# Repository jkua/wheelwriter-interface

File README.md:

# Low-level IBM Wheelwriter interface
This project is to build a low-level interface for an IBM Wheelwriter 
typewriter. This builds on work by 
[tofergregg](https://github.com/tofergregg/IBM-Wheelwriter-Hack), 
[RussellSenior](https://github.com/tofergregg/IBM-Wheelwriter-Hack/pull/11), 
and [jim11662418](https://github.com/jim11662418/wheelwriter-teletype) 
who figured out the internal serial communication bus and the protocol it uses.

This project was built and tested on an IBM Wheelwriter 3. Likely this will 
work on at least Series I Wheelwriters (3/5/6), and possibly later models as 
well.

## Architecture
This project consists of:

1. [Hardware interface module](pcb/) - this attaches to the back of the Wheelwriter as
the OEM printer option did, and connect to the 10-pin option connector located 
behind the 70 mm-wide hinged panel on the top rear of the typewriter. The core 
electronics are an [Arduino Nano RP2040 Connect](https://docs.arduino.cc/hardware/nano-rp2040-connect)
mounted on a custom PCB to interface with the Wheelwriter's option connector. 

3. [Arduino Wheelwriter driver](src/arduino/wheelwriter_interface) - this 
communicates with the Wheelwriter over the serial bus and provide low-level 
control of the typewriter, including platen and carriage positioning and 
typehead imprinting.

4. [REST API](docs/wwib_rest_api.md) service - the built-in WiFi connectivity 
on the Nano supports a web server which allows a modern computer, smartphone, 
or tablet to control the typewriter via the interface module.

5. [Python serial client](src/client) - PC client to talk to the Arduino and
allow it to send text to print as well as relay raw Wheelwriter commands. 

6. REST Client software - this software will demonstrate the use of the REST API

## Related work
[IBM-Wheelwriter-Hack](https://github.com/tofergregg/IBM-Wheelwriter-Hack) by 
Chris Gregg/[tofergregg](https://github.com/tofergregg) is what initially 
inspired me to look into Wheelwriters. His [videos](https://www.youtube.com/watch?v=Awxbu8y5cv8) 
[on](https://www.youtube.com/watch?v=0vrvDQmZcPI) 
[YouTube](https://www.youtube.com/watch?v=5FTS4fj5Im4) showed his work on 
reverse engineering the Wheelwriter's bus with a logic analyzer in about 2017.
His implementation bit-bangs a TX line to drive a N-channel MOSFET.

Be sure to check out his 
[Smith Corona typewriter to printer conversion](https://www.youtube.com/watch?v=le4C2HeNrdQ)!

Ryan Jarvis/[Cabalist](https://github.com/Cabalist) provided a 
[complete printwheel mapping](https://github.com/tofergregg/IBM-Wheelwriter-Hack/issues/5) 
for US language printwheels.

[Russell Senior](https://github.com/RussellSenior) made the connection that 
this is an Intel 8051 9-bit serial bus in mode 2 and provided a 
[great wiki page](https://github.com/RussellSenior/IBM-Wheelwriter-Hack/wiki/Bus-Protocol) 
describing a great deal of the command set.

[jim11662418](https://github.com/jim11662418) created implementations for 
the 8051 compatible [Dallas Semi DS89C440](https://github.com/jim11662418/wheelwriter-printer)
and [STC Micro STC15W4K32S4](https://github.com/jim11662418/wheelwriter-teletype)
that are very nice.

[MicroCoreLabs](https://github.com/MicroCoreLabs) created an 
[Lattice FPGA implementation](https://github.com/MicroCoreLabs/Projects/tree/master/Wheelwriter) 
and an [Arduino Leonardo implementation](https://github.com/MicroCoreLabs/Projects/tree/master/Wheelwriter2). 
Both implement a serial port that translates an ASCII character stream to motor 
controller commands. The Arduino implementation directly uses the ATmega32u4's 
UART an interestingly toggles the transmitter off when not sending. 
[Here's a YouTube video](https://www.youtube.com/watch?v=q8gCYw75E1A) of the 
FPGA version running.

[CadetWriter](https://github.com/IBM-1620/Cadetwriter) is an effort by Dave 
Babcock and Stephen Casner to interface to a Wheelwriter 1000 by instead 
sitting between the keyboard and the logic controller. This work was developed 
to build a general-purpose ASCII terminal.

### Derived work that builds on this project
[Generative Daily Planner](https://www.thingswemake.com/generative-daily-planner)
([Github](https://github.com/joshsucher/wheelwriter-gpt-agenda)) by Josh 
Sucher, is a "GPT-4-powered bot that ingests email, calendar and contacts from 
a range of sources (mainly Gmail, Gcal and iCloud) and outputs a daily agenda".

[wheelwriter6-printer](https://github.com/knicknackery/wheelwriter6-printer) 
by Brad/[knickknackery](https://github.com/knicknackery) ports this to a Pico W to interface a Wheelwriter 6 Series II with a CUPS 
driver to convert a Wheelwriter into a wireless printer! Includes a custom font 
for the WW6 Courier 12 wheel for a WYWISYG experience

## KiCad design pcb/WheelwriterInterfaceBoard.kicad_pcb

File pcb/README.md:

# Wheelwriter Interface Board

There are two versions of the Wheelwriter Interface Board. 

## v1 - Prototype breadboard
v1 ([schematic](wwib-v1/wwib-v1_schematic.pdf)) is the original prototype and 
was wired up on a solderless breadboard. This is what the code base was 
developed on as of 2024-09-21. This design is based on 
[tofergregg's](https://github.com/tofergregg/IBM-Wheelwriter-Hack) work.

## v2 - Expansion housing PCB
v2 ([schematic](wwib-v2/WheelwriterInterfaceBoard_schematic.pdf)) was designed 
to be a fabricated PCB and be the same size as the original Wheelwriter 
expansion boards, fit in the original expansion housing, and connect to the 
Wheelwriter expansion interface connector via a cable. This design has and 
isolated power supply and bus interface and is powered by the typewriter 
instead of the Arduino's USB port. 

*While I have not tested this design, [BlipRanger](https://github.com/BlipRanger)
has [reported success](https://github.com/jkua/wheelwriter-interface/issues/2#issuecomment-2415313493)!*

### Expansion cable
The expansion port on the Wheelwriter is a Molex SL series 10-pin shrouded 
header. A short cable needs to be built to connect the Wheelwriter expansion 
port to this interface board. A mating connector is Molex 50-57-9210 
(70066-0079). Contacts for 22-24 AWG wire are Molex 16-02-0102 (70058-0222). 

This design only uses +5V (pins 1, 2), GND (pins 3, 4), and BUS (pin 5). The 
rest are only for testing.

### v2 mounted in expansion housing

## Reference
### Original Wheelwriter expansion board
Image of the back of the board

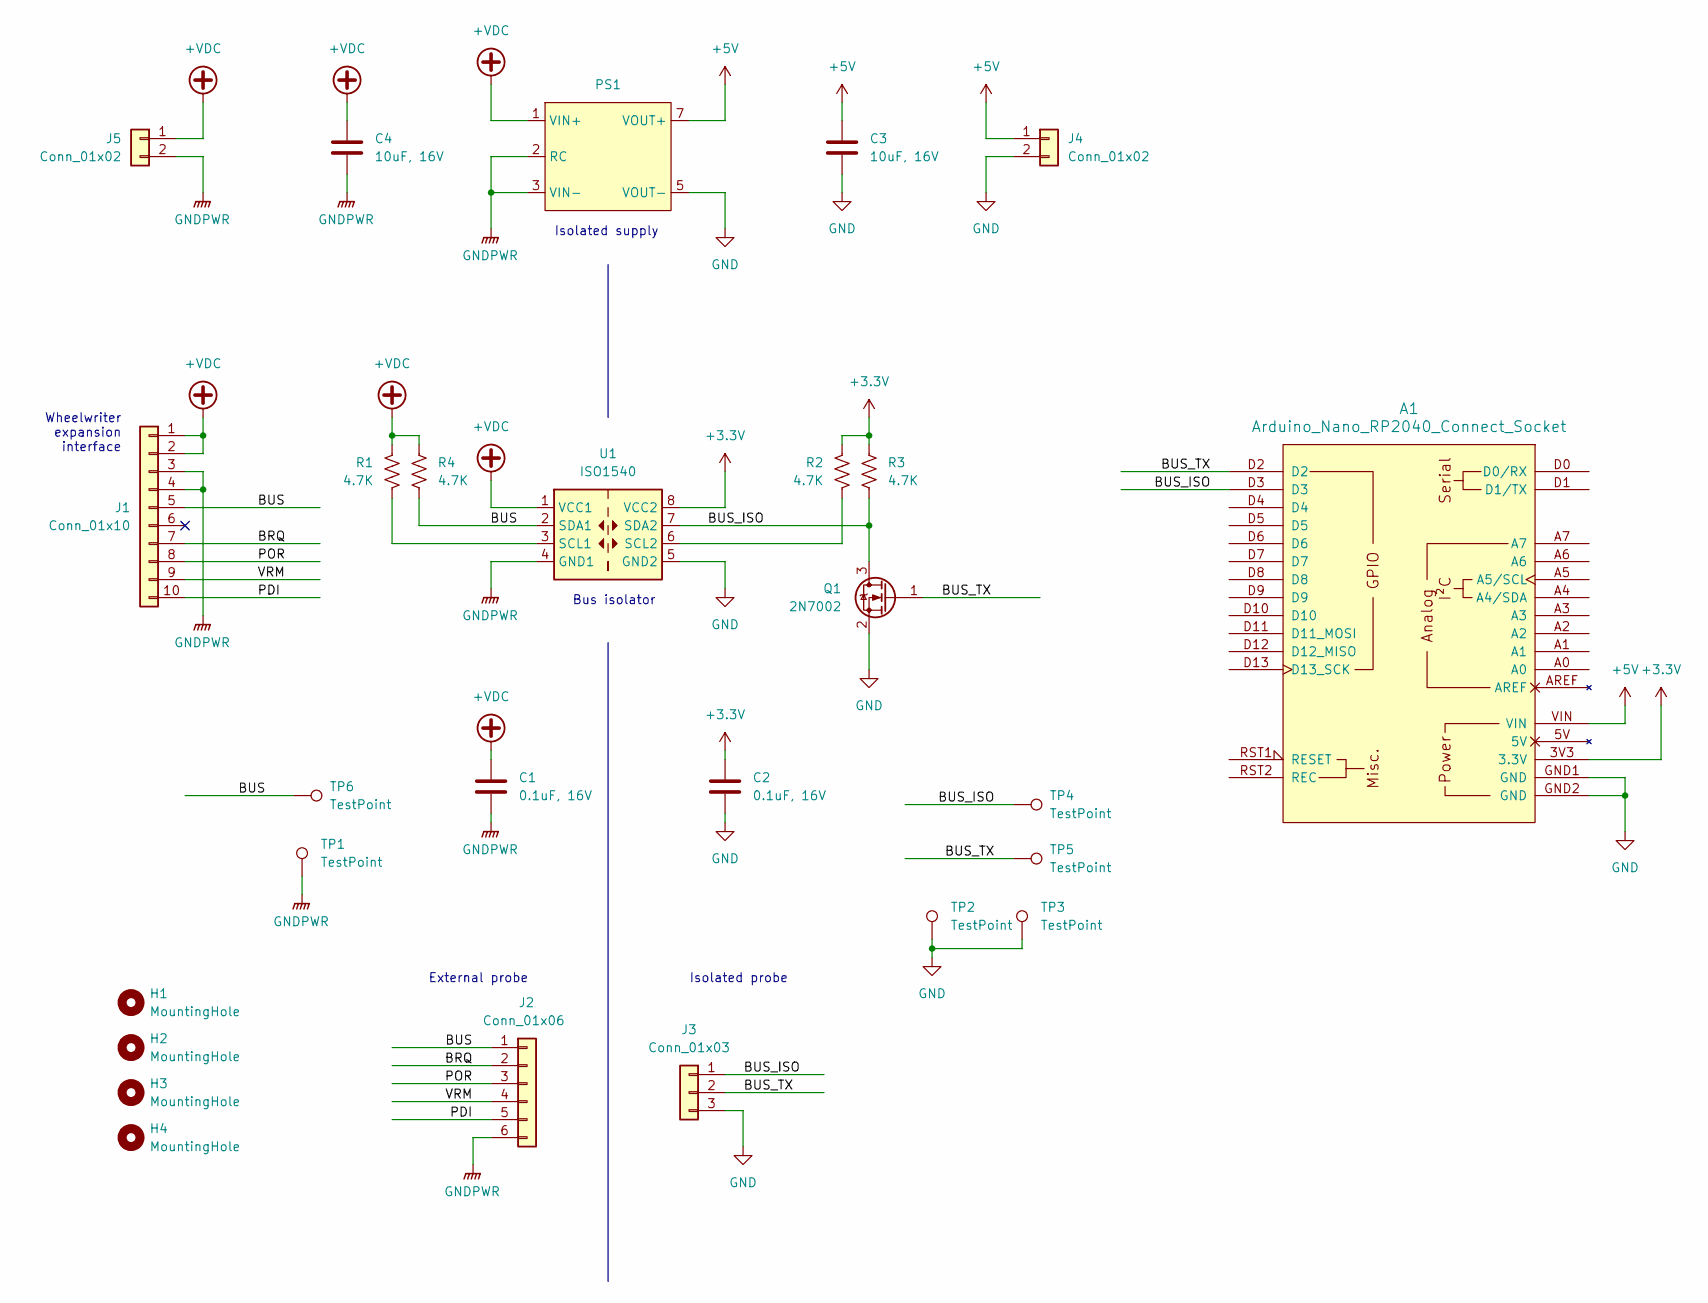
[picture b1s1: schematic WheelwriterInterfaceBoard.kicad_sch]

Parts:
A1: Arduino_Nano_RP2040_Connect_Socket; Arduino_Nano_Every_Socket
C1, C2: 0.1uF, 16V; C_0805_2012Metric_Pad1.18x1.45mm_HandSolder
C3, C4: 10uF, 16V; C_0805_2012Metric_Pad1.18x1.45mm_HandSolder
H1, H2, H3, H4: MountingHole; MountingHole_160mil
J1: Conn_01x10; Molex SL 70541-0009
J2: Conn_01x06; PinHeader_1x06_P2.54mm_Vertical
J3: Conn_01x03; PinHeader_1x03_P2.54mm_Vertical
J4, J5: Conn_01x02; PinHeader_1x02_P2.54mm_Vertical
PS1: Converter_DCDC_TDK-Lambda_CC10(R)
Q1: 2N7002; SOT-23
R1, R2, R3, R4: 4.7K; R_0805_2012Metric_Pad1.20x1.40mm_HandSolder
TP1, TP2, TP3, TP4, TP5, TP6: TestPoint; TestPoint_Keystone_5005-5009_Compact
U1: ISO1540; SOIC-8_3.9x4.9mm_P1.27mm

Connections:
+3.3V: A1.3V3 (3.3V), C2.1, R2.1, R3.1, U1.8 (VCC2)
+5V: A1.VIN, C3.1, J4.1, PS1.7 (VOUT+)
+VDC: C1.1, C4.1, J1.1, J1.2, J5.1, PS1.1 (VIN+), R1.1, R4.1, U1.1 (VCC1)
/BRQ: J1.7, J2.2
/BUS: J1.5, J2.1, R4.2, TP6.1, U1.2 (SDA1)
/BUS_ISO: A1.D3, J3.1, Q1.3 (D), R3.2, TP4.1, U1.7 (SDA2)
/BUS_TX: A1.D2, J3.2, Q1.1 (G), TP5.1
/PDI: J1.10, J2.5
/POR: J1.8, J2.3
/VRM: J1.9, J2.4
GND: A1.GND1 (GND), A1.GND2 (GND), C2.2, C3.2, J3.3, J4.2, PS1.5 (VOUT-), Q1.2 (S), TP2.1, TP3.1, U1.5 (GND2)
GNDPWR: C1.2, C4.2, J1.3, J1.4, J2.6, J5.2, PS1.2 (RC), PS1.3 (VIN-), TP1.1, U1.4 (GND1)
unnamed: R1.2, U1.3 (SCL1)
unnamed: R2.2, U1.6 (SCL2)

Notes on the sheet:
External probe
Bus isolator
Isolated supply
Wheelwriter expansion interface
Isolated probe

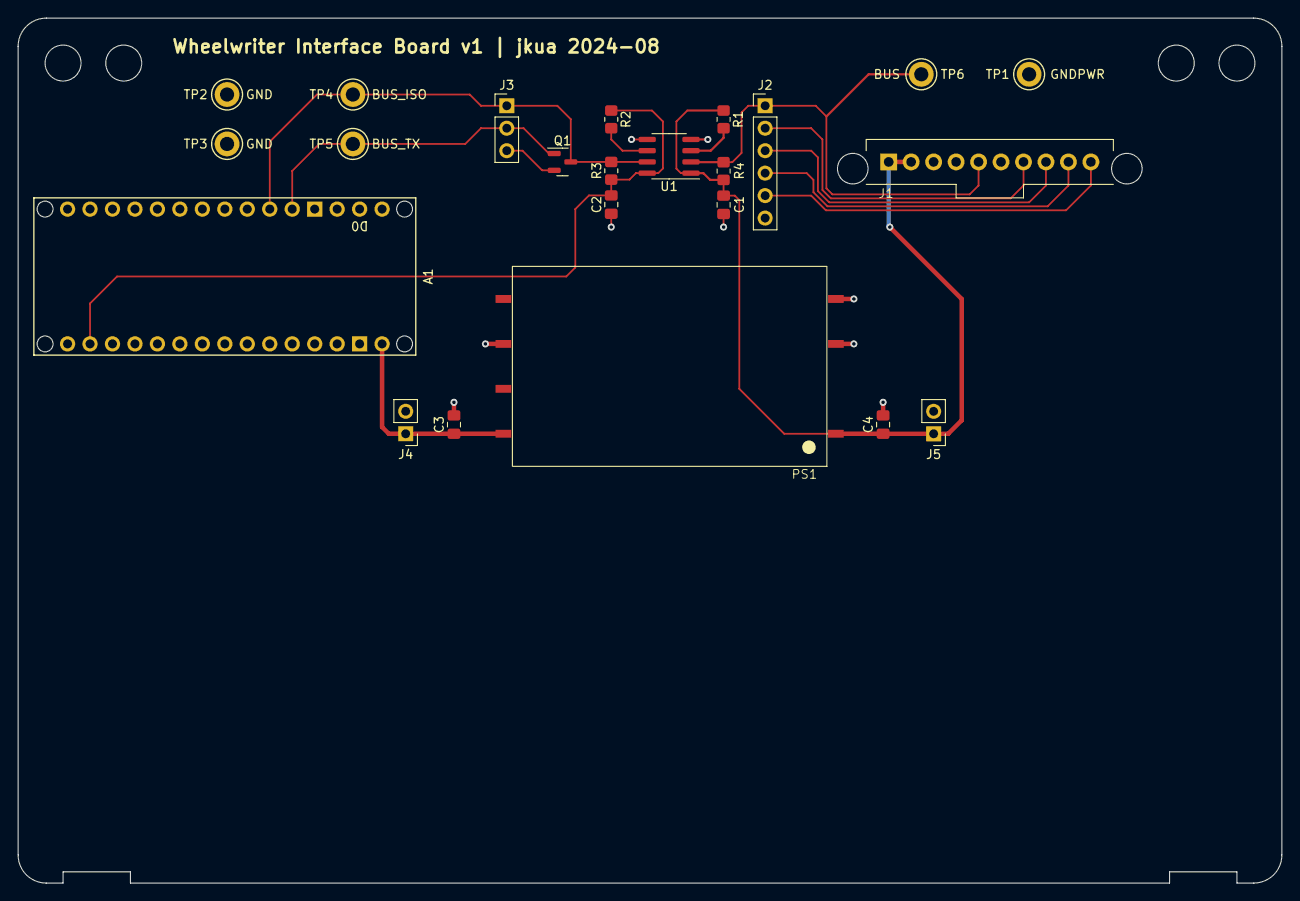
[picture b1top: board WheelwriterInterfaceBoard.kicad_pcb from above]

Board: 2 copper layers, 142.9 x 97.8 mm, 27 parts (0 on the bottom side), 14 nets.

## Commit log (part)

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2023-01-29 Added README
2023-01-29 Added more related work to the README
2023-01-29 Added Wheelwriter hardware doc
2023-01-29 Add connector labels to hardware block diagram
2023-02-01 Initial Arduino Nano RP2040 Connect code. Basic interface to send commands to the typewriter implemented
2023-02-01 Added docs for the Wheelwriter bus and the Arduino code
2023-02-02 Add inverted tx
2023-02-06 TX works - can generate circle test! RX does not work
2023-02-07 Added all-character test and typestyles (bold/underline)
2023-02-07 Minor test string fix
2023-02-07 Refactored character test to be less redundant
2023-02-07 Added links to additional resources in README and expanded on the bus protocol description
2023-02-07 Minor edits to README
2023-02-08 Added MicroCoreLabs related work to README
2023-02-08 Refactored main function to implement basic CLI. Also added type function to pass strings on the USB interface to the typewriter
2023-02-08 Moved uart_9bit files to a separate folder
2023-02-09 Added raw and printwheel sample modes to the Arduino
    Also added carriage position tracking to automate carriage returns.
    Added character space automation and linefeed automation.
    Added sendText.py Python client to upload text to the typewriter.
    This includes some sample text.
2023-02-09 Added .gitignore
2023-02-10 UART RX works!
    Implemented ACK and response reads and added typewriter status
    checks so that the delays can be stripped out and typing happens
    at full speed.
    Loopback and model query tests added. Type function seems to be
    broken. Occasionally getting the odd ACK error getting the address
    indicating a sync error. Need to disable the receiver during TX.
2023-02-10 Disabled the Wheelwriter::queryOperation() method. It's not a query and it's unclear what it actually does
2023-02-10 Added buffer test - not tested
2023-02-11 Stripped out the waitReady() calls as the typewriter appears to have a reasonably deep command buffer. Also fixed the queryPrintwheel() and queryStatus() calls to actually output something
2023-02-11 sendText.py working now
    Added ANSI test file. Removed title underline from other text samples.
    Added Wheelwriter::readFlush() to try to clean up/diagnose a problem
    where the serial comms get out of sync and misses a read.
2023-02-12 Added char/line spacing setup based on reading the wheel pitch.Also added a command read function
2023-02-12 Added keyboard read function
2023-12-10 Add keyboard selection support and ASCII keyboards. Need to consider Unicode for extended Latin and non-Latin support
2023-12-11 Added read flushes to synchronize Arduino with typewriter. Also added printwheel mappings
2023-12-11 Added USSR/Cyrillic (231) keyboard
2024-07-06 Added PCB board outline
2024-07-06 Added scan of PCB
2024-08-04 PCB v1.0
2024-08-10 Added schematic PDF and image of PCB
2024-08-10 Added documentation for the WWIB serial protocol
2024-08-10 Minor cleanup of the WWIB serial protocol doc
2024-08-19 Arduino: typeFunction() takes useCaratAsControl as an argument
2024-08-19 Arduino - Wheelwriter.cpp fixed and cleaned up readCommand()
2024-08-20 Moved Wheelwriter Interface Board v2 to a subfolder of pcb and added the V1 schematic
2024-08-20 Added pcb README
2024-08-20 Added image to pcb README
2024-08-20 sendText: Added noPrintableEscape option to prevent trigging escape sequences when sending arbitrary ASCII text
2024-08-24 Added draft of the relay protocol document
2024-08-24 Restructured the relay protocol doc and added relay configuration commands
2024-08-24 Relay protocol doc: bullets
2024-08-24 Relay protocol doc: example ticks
2024-08-24 Relay protocol doc: get/set address command byte typos
2024-08-24 Relay protocol doc: panic response
2024-08-24 Relay protocol doc: significant modifications to apply more consistent byte structures
2024-08-24 Relay protocol doc: minor fixes
2024-08-24 Relay protocol doc: Extended the response message to echo the original command byte
2024-08-25 Implemented command relay function - tested with query command
2024-08-25 Extended relayTest to test abbreviated and batch modes - works
2024-08-26 Added the Python WheelwriterClent class and scripts readBus and relayClientTest
2024-08-26 Moved the old WheelwriterClient class to WheelwriterInterface and created a new WheelwriterClient class. Added the clientTest script
2024-08-27 Extended the Python WheelwriterClient with essentially all the commands in the Arduino Wheelwriter class. clientTest now also executes the circle test.
2024-08-28 Added sinusoidal client example
2024-08-30 Add venv to .gitignore
2024-09-02 Added printWheelPositions.py to send wheel positions rather than ASCII characters to the typewriter
2024-09-21 Added images of the Wheelwriter expansion housing and some expansion cable information
2024-09-21 Minor README cleanup
2024-09-22 Refactored sendText.py to use WheelwriterInterface
2024-09-22 Make sendText.py executable
2024-09-23 Added support for fractional character/line space movements in the Python WheelwriterClient. Also added interleave support in printWheelPositions.py
2024-10-21 Added parameter storage to the internal flash in preparation for WiFi support
2024-10-30 Add REST API over WiFi using PicoRest and WiFiNINA
2024-10-31 Refactored typeFunction() to move the majority of processing into the Wheelwriter::TypeStream class so that the REST API can also use it. Also moved the bufferTest() into Wheelwriter as well and fixe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
2024-11-01 Fixed an issue in Wheelwriter::TypeStream::parseEscape() where some invalid CSI escape sequences were not caught
2024-11-01 Added /characterTest, /circleTest, /printwheelSample, and /query endpoints to the REST API. Added ParameterString class to handle parsing delimited lists of parameters
2024-11-01 Add REST documentation
2024-11-01 More REST documentation
2024-11-02 Added /readLine endpoint to read a line from the typewriter
2024-11-02 Added copyright strings to headers
2024-11-02 Added BSD 3-clause license
2024-11-02 Added 'corrected' option to /readLine
2024-11-10 Added code + key mappings and initial work for in-typewriter terminal to access config and other functions without a separate computer
2024-11-10 Refactored Wheelwriter::sendCommand() methods and added readFlush() and queryStatus() before all commands. Stripped out some superfluous readFlush() calls in the rest of the code
2024-11-12 Added WheelwriterCommandLineInterface class to handle stuff. Changed code+key mappings to just key mappings. Added documentation on Wheelwriter bus commands.
2024-11-19 Make return, space, backspace detection more robust until key code translation works. Also handle POST requests with no content
2024-12-15 wheelwriterClient TypeMode - Added back support for keyboard and noPrintableEscape options that were lost in the refactor
2024-12-15 Updated WW bus doc with information about 0x09 - impression control
